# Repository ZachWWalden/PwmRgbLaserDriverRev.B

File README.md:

# PwmRgbLaserDriverRev.B
This repository contains the Kicad files for a PCB that drives a 3 segment full color laser assembly that has an adjustable white point. It can be modulated with either Pulse-Width Modulation with a 5V digital signal at each segments input terminal. It may also be modulated using a simple analog voltage at each input terminal.

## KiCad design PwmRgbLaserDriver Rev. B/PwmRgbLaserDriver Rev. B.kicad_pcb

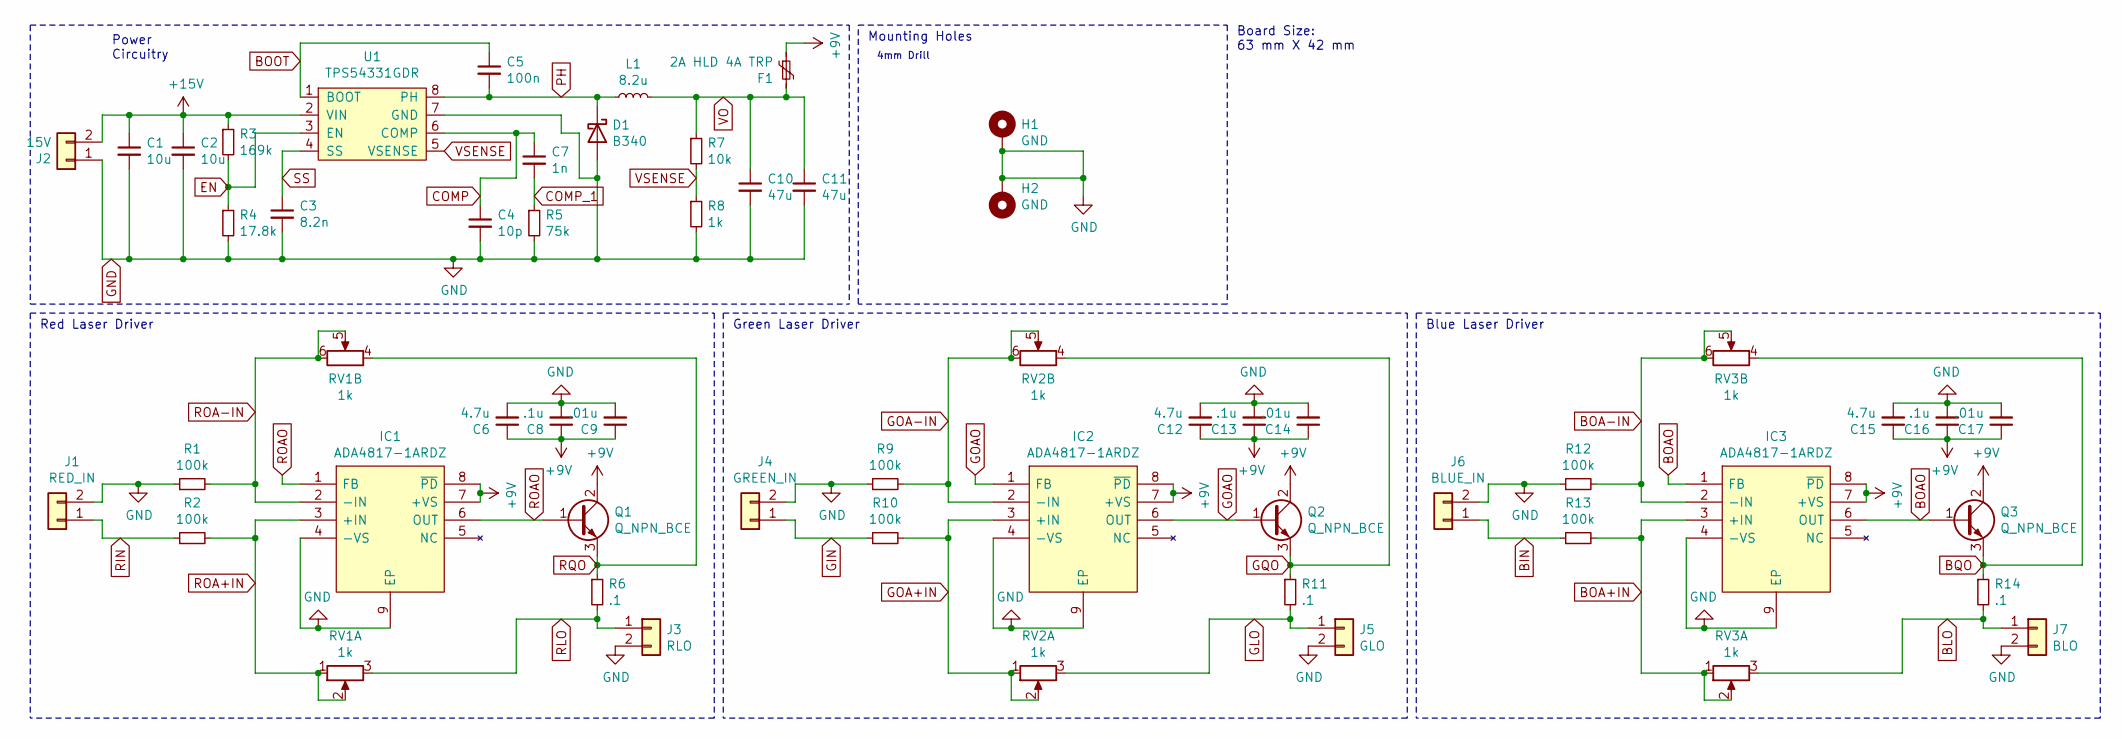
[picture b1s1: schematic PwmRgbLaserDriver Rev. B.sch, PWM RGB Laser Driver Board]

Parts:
C1, C2: 10u; C_0805_2012Metric_Pad1.18x1.45mm_HandSolder
C3: 8.2n; C_0402_1005Metric_Pad0.74x0.62mm_HandSolder
C4: 10p; C_0402_1005Metric_Pad0.74x0.62mm_HandSolder
C5: 100n; C_0402_1005Metric_Pad0.74x0.62mm_HandSolder
C6, C12, C15: 4.7u; C_0805_2012Metric_Pad1.18x1.45mm_HandSolder
C7: 1n; C_0402_1005Metric_Pad0.74x0.62mm_HandSolder
C8, C13, C16: .1u; C_0402_1005Metric_Pad0.74x0.62mm_HandSolder
C9, C14, C17: .01u; C_0402_1005Metric_Pad0.74x0.62mm_HandSolder
C10, C11: 47u; C_1210_3225Metric_Pad1.33x2.70mm_HandSolder
D1: B340; D_SMA_Handsoldering
F1: 2A HLD 4A TRP; Fuse_2920_7451Metric_Pad2.10x5.45mm_HandSolder
H1, H2: GND; 4mm Mounting Hole
IC1, IC2, IC3: ADA4817-1ARDZ; SOIC127P600X175-9N; Mouser Part Number 584-ADA4817-1ARDZ
J1: RED_IN; PinHeader_1x02_P2.54mm_Vertical
J2: 15V; PinHeader_1x02_P2.54mm_Vertical
J3: RLO; PinHeader_1x02_P2.54mm_Vertical
J4: GREEN_IN; PinHeader_1x02_P2.54mm_Vertical
J5: GLO; PinHeader_1x02_P2.54mm_Vertical
J6: BLUE_IN; PinHeader_1x02_P2.54mm_Vertical
J7: BLO; PinHeader_1x02_P2.54mm_Vertical
L1: 8.2u; Bourns SRP6540
Q1, Q2, Q3: Q_NPN_BCE; SOT-89-3_Handsoldering
R1, R2, R9, R10, R12, R13: 100k; R_0402_1005Metric_Pad0.72x0.64mm_HandSolder
R3: 169k; R_0402_1005Metric_Pad0.72x0.64mm_HandSolder
R4: 17.8k; R_0402_1005Metric_Pad0.72x0.64mm_HandSolder
R5: 75k; R_0402_1005Metric_Pad0.72x0.64mm_HandSolder
R6, R11, R14: .1; R_0402_1005Metric_Pad0.72x0.64mm_HandSolder
R7: 10k; R_0805_2012Metric_Pad1.20x1.40mm_HandSolder
R8: 1k; R_0603_1608Metric_Pad0.98x0.95mm_HandSolder
RV1, RV2, RV3: 1k; DualGangPotAmazon
U1: TPS54331GDR; SOIC-8_3.9x4.9mm_P1.27mm

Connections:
+9V: C6.1, C8.1, C9.1, C12.1, C13.1, C14.1, C15.1, C16.1, C17.1, F1.1, IC1.7 (+VS), IC1.8 (~PD), IC2.7 (+VS), IC2.8 (~PD), IC3.7 (+VS), IC3.8 (~PD), Q1.2 (C), Q2.2 (C), Q3.2 (C)
+15V: C1.1, C2.1, J2.2, R3.1, U1.2 (VIN)
BIN: J6.1, R13.1
BLO: J7.1, R14.2, RV3.3
BOA+IN: IC3.3 (+IN), R13.2, RV3.1, RV3.2
BOA-IN: IC3.2 (-IN), R12.2, RV3.5, RV3.6
BOAO: IC3.1 (FB), IC3.6 (OUT), Q3.1 (B)
BOOT: C5.1, U1.1 (BOOT)
BQO: Q3.3 (E), R14.1, RV3.4
COMP: C4.1, C7.1, U1.6 (COMP)
COMP_1: C7.2, R5.1
EN: R3.2, R4.1, U1.3 (EN)
GIN: J4.1, R10.1
GLO: J5.1, R11.2, RV2.3
GND: C1.2, C2.2, C3.2, C4.2, C6.2, C8.2, C9.2, C10.2, C11.2, C12.2, C13.2, C14.2, C15.2, C16.2, C17.2, D1.2 (A), H1.1, H2.1, IC1.4 (-VS), IC1.9 (EP), IC2.4 (-VS), IC2.9 (EP), IC3.4 (-VS), IC3.9 (EP), J1.2, J2.1, J3.2, J4.2, J5.2, J6.2, J7.2, R1.1, R4.2, R5.2, R8.2, R9.1, R12.1, U1.7 (GND)
GOA+IN: IC2.3 (+IN), R10.2, RV2.1, RV2.2
GOA-IN: IC2.2 (-IN), R9.2, RV2.5, RV2.6
GOAO: IC2.1 (FB), IC2.6 (OUT), Q2.1 (B)
GQO: Q2.3 (E), R11.1, RV2.4
PH: C5.2, D1.1 (K), L1.1, U1.8 (PH)
RIN: J1.1, R2.1
RLO: J3.1, R6.2, RV1.3
ROA+IN: IC1.3 (+IN), R2.2, RV1.1, RV1.2
ROA-IN: IC1.2 (-IN), R1.2, RV1.5, RV1.6
ROAO: IC1.1 (FB), IC1.6 (OUT), Q1.1 (B)
RQO: Q1.3 (E), R6.1, RV1.4
SS: C3.1, U1.4 (SS)
VO: C10.1, C11.1, F1.2, L1.2, R7.1
VSENSE: R7.2, R8.1, U1.5 (VSENSE)

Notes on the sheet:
Red Laser Driver
Green Laser Driver
Blue Laser Driver
Board Size: 63 mm X 42 mm
Power Circuitry
Mounting Holes
4mm Drill

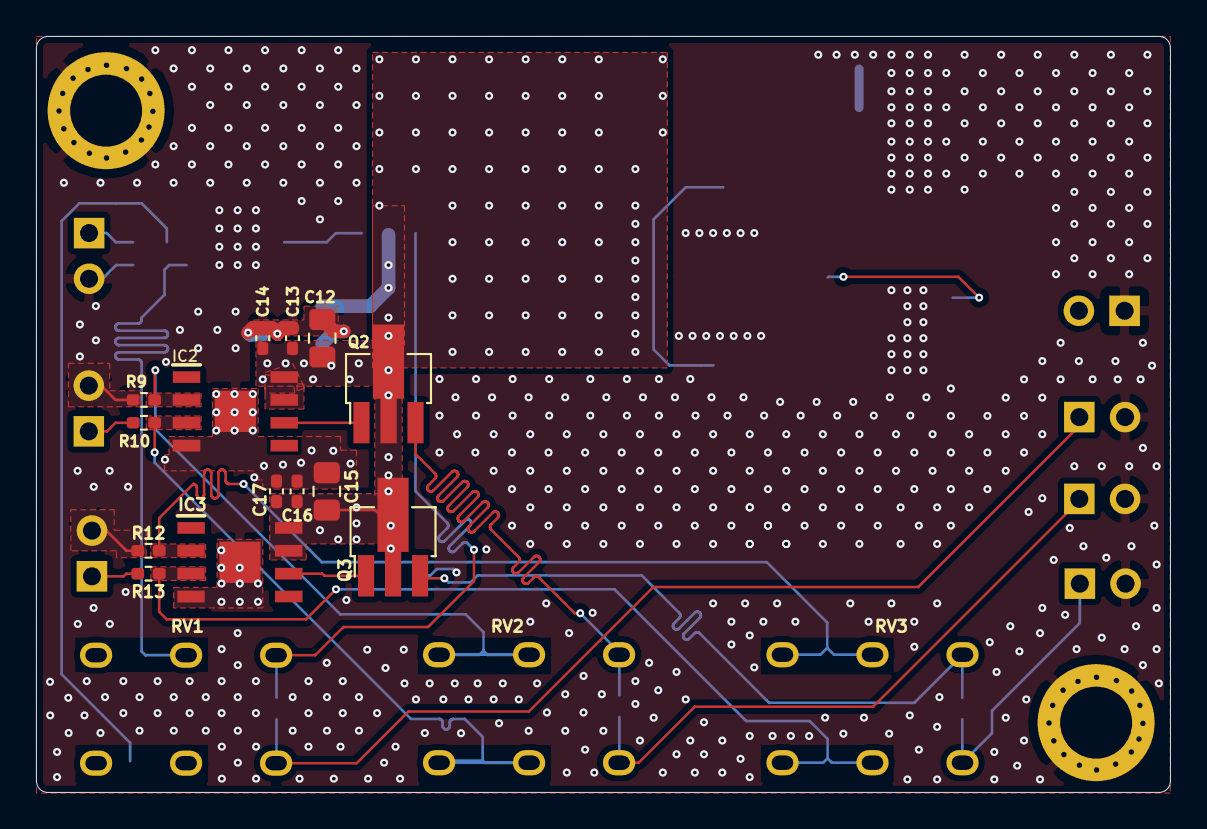
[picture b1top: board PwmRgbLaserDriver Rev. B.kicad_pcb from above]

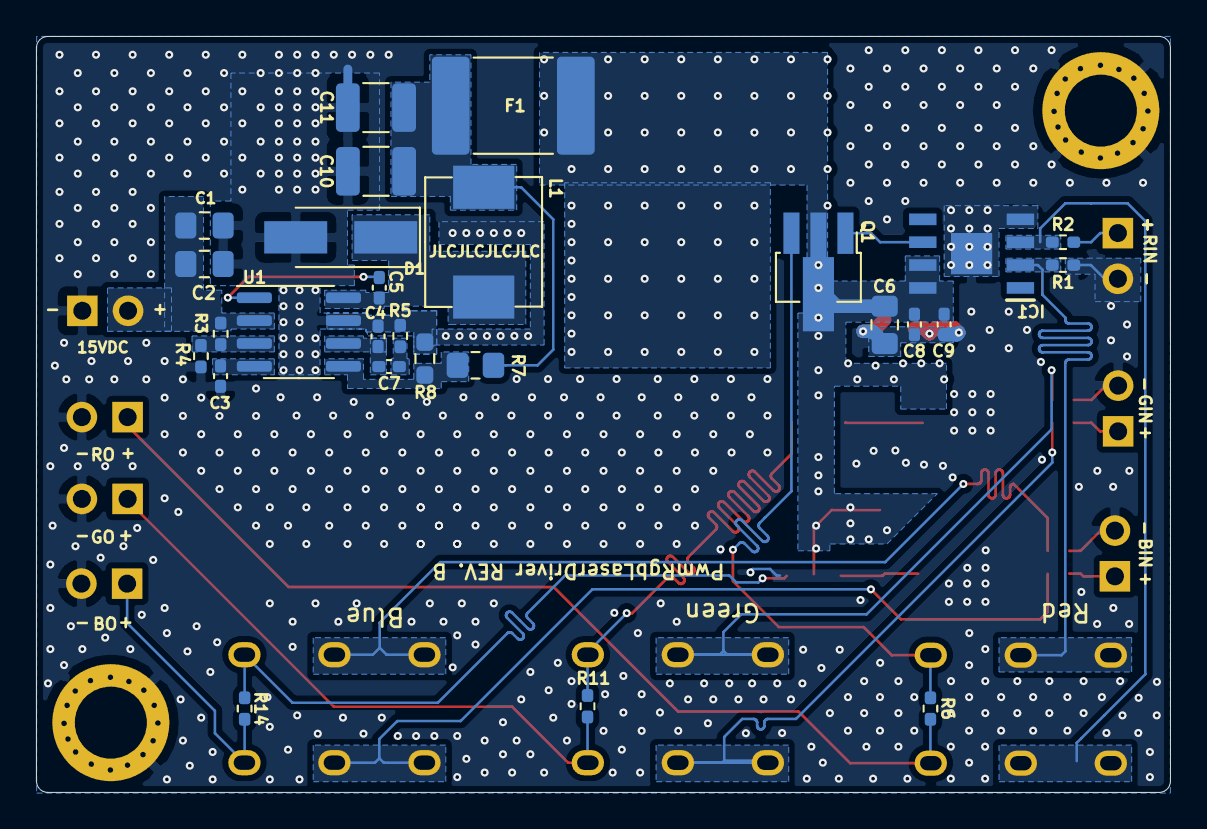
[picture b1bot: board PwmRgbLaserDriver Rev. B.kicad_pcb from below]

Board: 4 copper layers, 63.0 x 42.0 mm, 53 parts (27 on the bottom side), 29 nets.

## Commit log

2021-06-30 Current Source Schematic
    This commit contains the schematic for the constant current source for each laser diode.
2021-06-30 Switching Converter Added
    This commit adds the switching converter for power.
2021-06-30 Small Fixes
    Added Enable pin resistor divider on switcher. Fixed grounding issues in drivers
2021-06-30 TO-DO Update
2021-07-01 Fixed Some Errors
    Fixed some errors and updated the to-do list.
2021-07-01 Some Footprints Added
2021-07-02 Footprints, SMPS Placement
    Footprints have now been fully assigned.
    The components for the 27W SMPS have been placed.
2021-07-09 Placement And Some Routhing
    Placed all components and routed the important analog signal traces.
    Power remains unfinished along with precise placement of the mounting holes.
2021-07-10 Small Update
    Nothing Much
2021-07-13 PDN Additions
    All copper pours have been placed. Some PDN stitching vias have been placed.
2021-07-13 PDN & Silk Screen Improvements
    Small additions
2021-07-14 Board Finished
    Board has been completed. PDN finished, Silk Screen cleaned up.
